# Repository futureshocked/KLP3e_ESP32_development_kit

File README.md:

# KLP3e ESP32 development kit, a Kicad project

This is the repository for the "ESP32 Devkit clone" project.

This is one of the projects from the course [KiCad Like a Pro, 3rd edition](https://techexplorations.com/so/kicad-like-a-pro-3rd-edition/).

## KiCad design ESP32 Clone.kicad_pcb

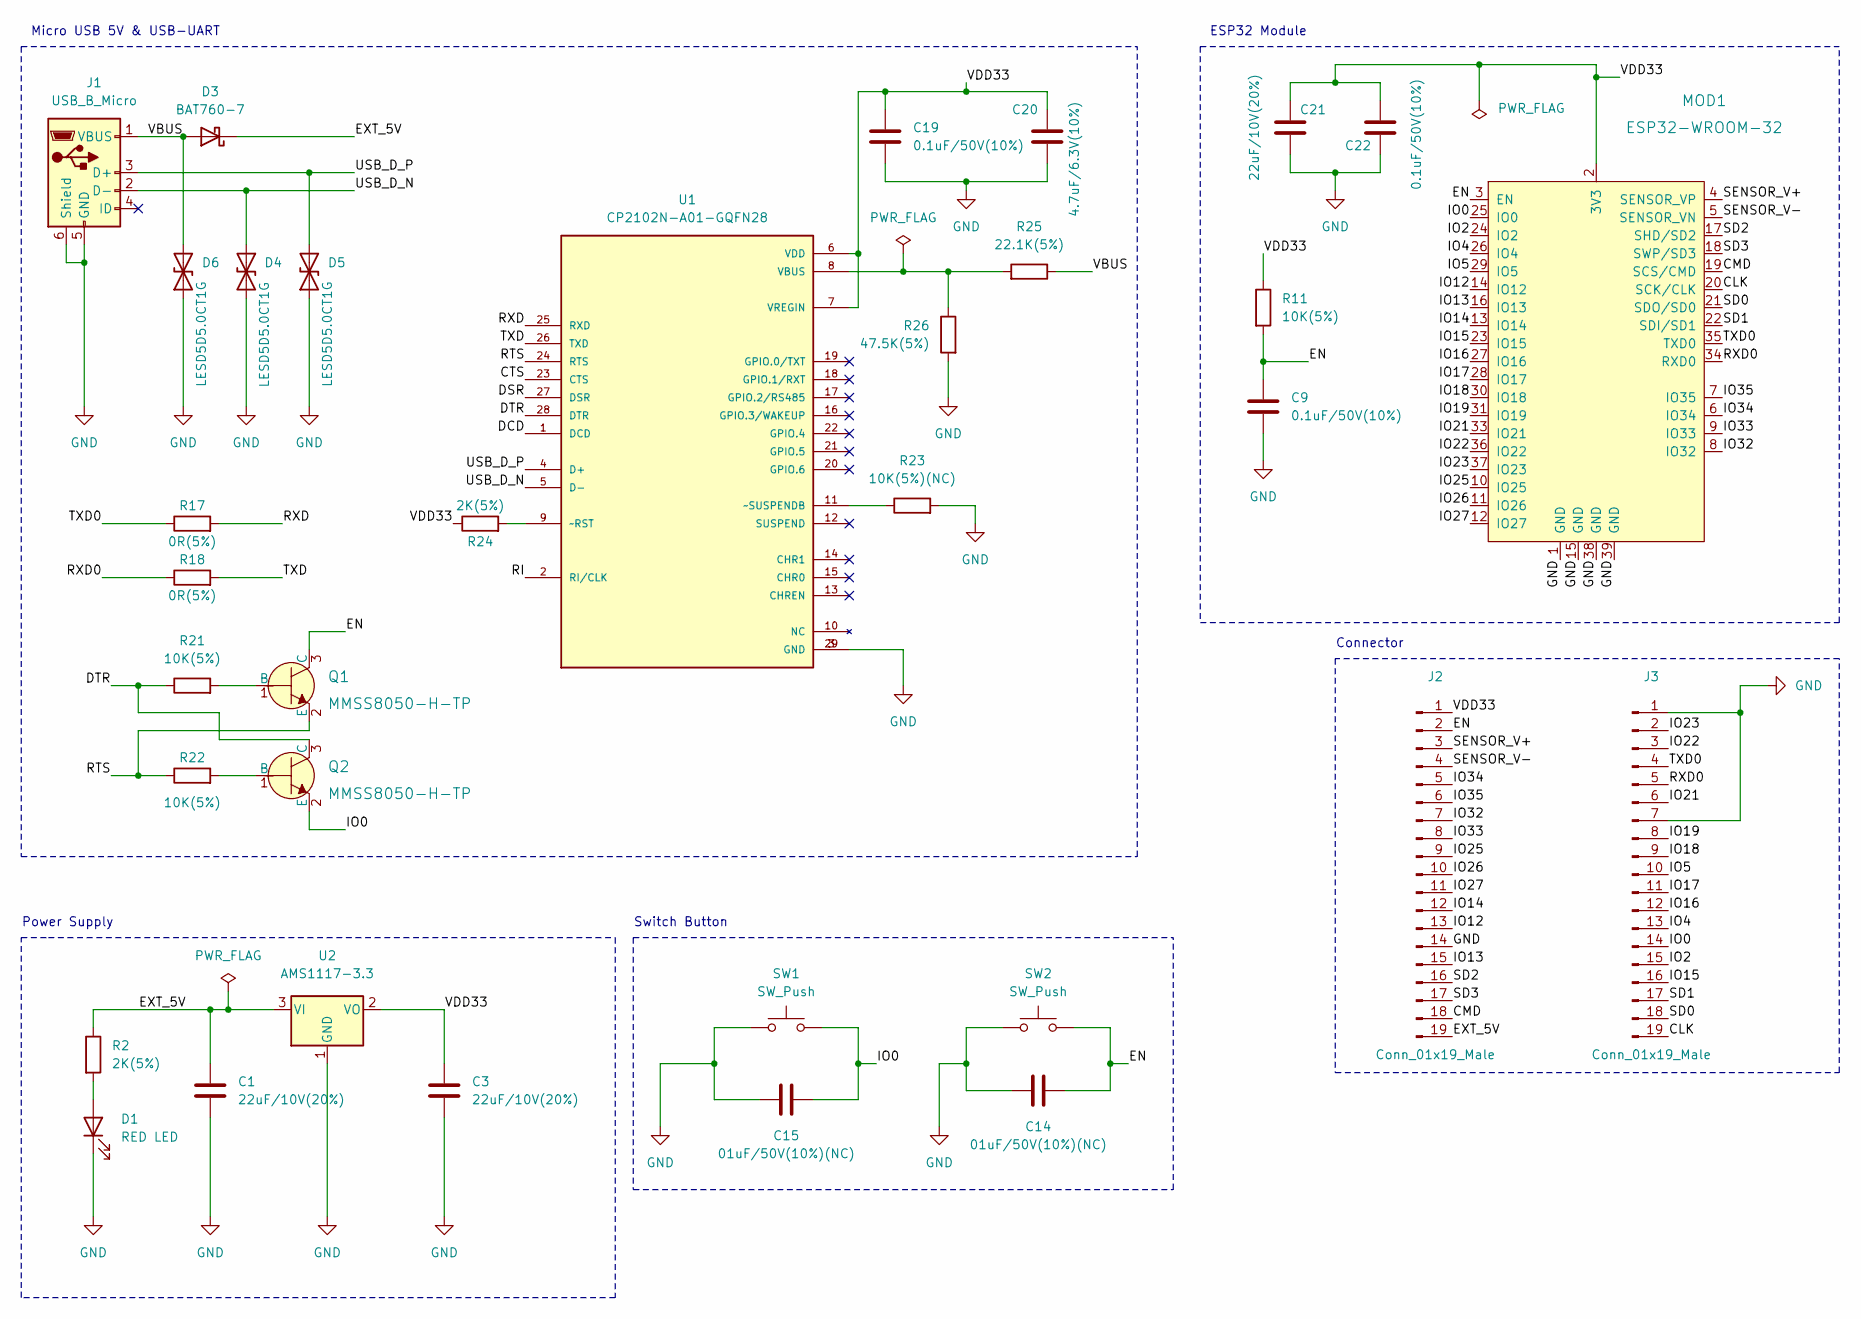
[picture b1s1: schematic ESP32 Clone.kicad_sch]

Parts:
C1, C3, C21: 22uF/10V(20%); C_0603_1608Metric
C9, C19, C22: 0.1uF/50V(10%); C_0402_1005Metric
C14, C15: 01uF/50V(10%)(NC); C_0402_1005Metric
C20: 4.7uF/6.3V(10%); C_0402_1005Metric
D1: RED LED; LED_0201_0603Metric
D3: BAT760-7; D_SOD-323
D4, D5, D6: LESD5D5.0CT1G; D_SOD-523
J1: USB_B_Micro; USB_Micro-AB_Molex_47590-0001
J2, J3: Conn_01x19_Male; PinHeader_1x19_P2.54mm_Vertical
MOD1: ESP32-WROOM-32; ESP32-WROOM-32D; MPN ESP32-WROOM-32; Digi-Key_PN 1904-1010-1-ND
Q1, Q2: MMSS8050-H-TP; SOT-23-3; MPN MMSS8050-H-TP; Digi-Key_PN MMSS8050-H-TPMSCT-ND
R2, R24: 2K(5%); R_01005_0402Metric
R11: 10K(5%); R_01005_0402Metric
R17, R18: 0R(5%); R_01005_0402Metric
R21, R22: 10K(5%); R_0402_1005Metric
R23: 10K(5%)(NC); R_01005_0402Metric
R25: 22.1K(5%); R_01005_0402Metric
R26: 47.5K(5%); R_01005_0402Metric
SW1, SW2: SW_Push; SW_B3S-1000P
U1: CP2102N-A01-GQFN28; TQFN-28-1EP_5x5mm_P0.5mm_EP2.7x2.7mm; PARTREV 1.0
U2: AMS1117-3.3; SOT-223-3_TabPin2

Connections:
/CLK: J3.19, MOD1.20 (SCK/CLK)
/CMD: J2.18, MOD1.19 (SCS/CMD)
/CTS: U1.23 (CTS)
/DCD: U1.1 (DCD)
/DSR: U1.27 (DSR)
/DTR: Q2.3 (C), R21.1, U1.28 (DTR)
/EN: C9.1, C14.2, J2.2, MOD1.3 (EN), Q1.3 (C), R11.2, SW2.2
/EXT_5V: C1.1, D3.1 (K), J2.19, R2.1, U2.3 (VI)
/IO0: C15.2, J3.14, MOD1.25 (IO0), Q2.2 (E), SW1.2
/IO2: J3.15, MOD1.24 (IO2)
/IO4: J3.13, MOD1.26 (IO4)
/IO5: J3.10, MOD1.29 (IO5)
/IO12: J2.13, MOD1.14 (IO12)
/IO13: J2.15, MOD1.16 (IO13)
/IO14: J2.12, MOD1.13 (IO14)
/IO15: J3.16, MOD1.23 (IO15)
/IO16: J3.12, MOD1.27 (IO16)
/IO17: J3.11, MOD1.28 (IO17)
/IO18: J3.9, MOD1.30 (IO18)
/IO19: J3.8, MOD1.31 (IO19)
/IO21: J3.6, MOD1.33 (IO21)
/IO22: J3.3, MOD1.36 (IO22)
/IO23: J3.2, MOD1.37 (IO23)
/IO25: J2.9, MOD1.10 (IO25)
/IO26: J2.10, MOD1.11 (IO26)
/IO27: J2.11, MOD1.12 (IO27)
/IO32: J2.7, MOD1.8 (IO32)
/IO33: J2.8, MOD1.9 (IO33)
/IO34: J2.5, MOD1.6 (IO34)
/IO35: J2.6, MOD1.7 (IO35)
/RI: U1.2 (RI/CLK)
/RTS: Q1.2 (E), R22.1, U1.24 (RTS)
/RXD: R17.2, U1.25 (RXD)
/RXD0: J3.5, MOD1.34 (RXD0), R18.1
/SD0: J3.18, MOD1.21 (SDO/SD0)
/SD1: J3.17, MOD1.22 (SDI/SD1)
/SD2: J2.16, MOD1.17 (SHD/SD2)
/SD3: J2.17, MOD1.18 (SWP/SD3)
/SENSOR_V+: J2.3, MOD1.4 (SENSOR_VP)
/SENSOR_V-: J2.4, MOD1.5 (SENSOR_VN)
/TXD: R18.2, U1.26 (TXD)
/TXD0: J3.4, MOD1.35 (TXD0), R17.1
/USB_D_N: D4.1 (A1), J1.2 (D-), U1.5 (D-)
/USB_D_P: D5.2 (A2), J1.3 (D+), U1.4 (D+)
/VBUS: D3.2 (A), D6.2 (A2), J1.1 (VBUS), R25.1
/VDD33: C3.1, C19.1, C20.1, C21.1, C22.1, J2.1, MOD1.2 (3V3), R11.1, R24.1, U1.6 (VDD), U1.7 (VREGIN), U2.2 (VO)
GND: C1.2, C3.2, C9.2, C14.1, C15.1, C19.2, C20.2, C21.2, C22.2, D1.1 (K), D4.2 (A2), D5.1 (A1), D6.1 (A1), J1.5 (GND), J1.6 (Shield), J2.14, J3.1, J3.7, MOD1.1 (GND), MOD1.15 (GND), MOD1.38 (GND), MOD1.39 (GND), R23.2, R26.2, SW1.1, SW2.1, U1.3 (GND), U1.29 (GND), U2.1 (GND)
unnamed: R25.2, R26.1, U1.8 (VBUS)
unnamed: D1.2 (A), R2.2
unnamed: Q1.1 (B), R21.2
unnamed: Q2.1 (B), R22.2
unnamed: R24.2, U1.9 (~RST)
unnamed: R23.1, U1.11 (~SUSPENDB)

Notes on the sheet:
Micro USB 5V & USB-UART
Connector
Power Supply
Switch Button
ESP32 Module

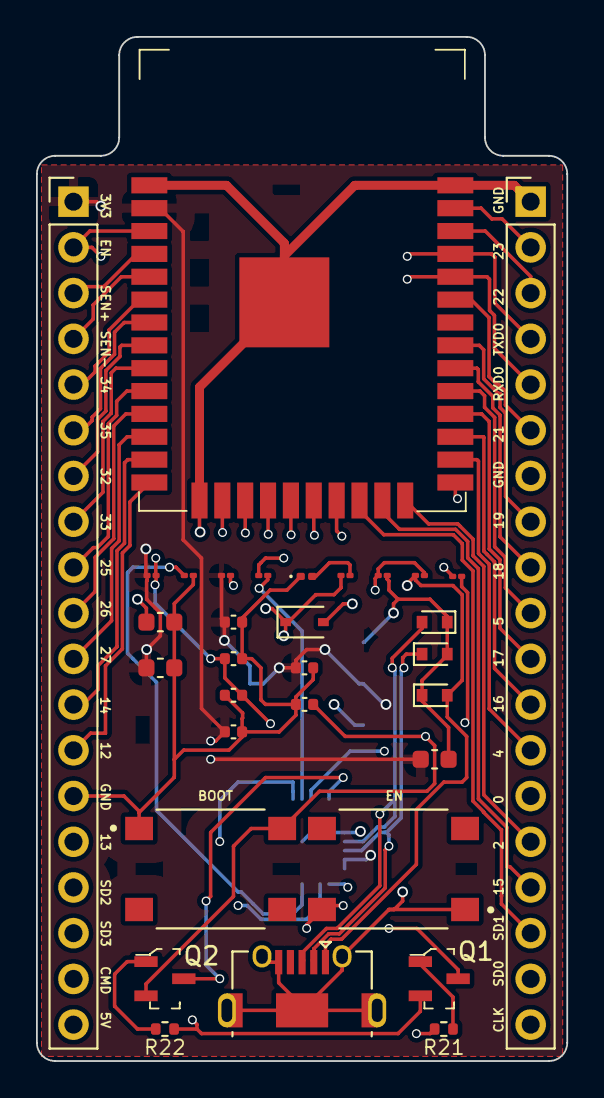
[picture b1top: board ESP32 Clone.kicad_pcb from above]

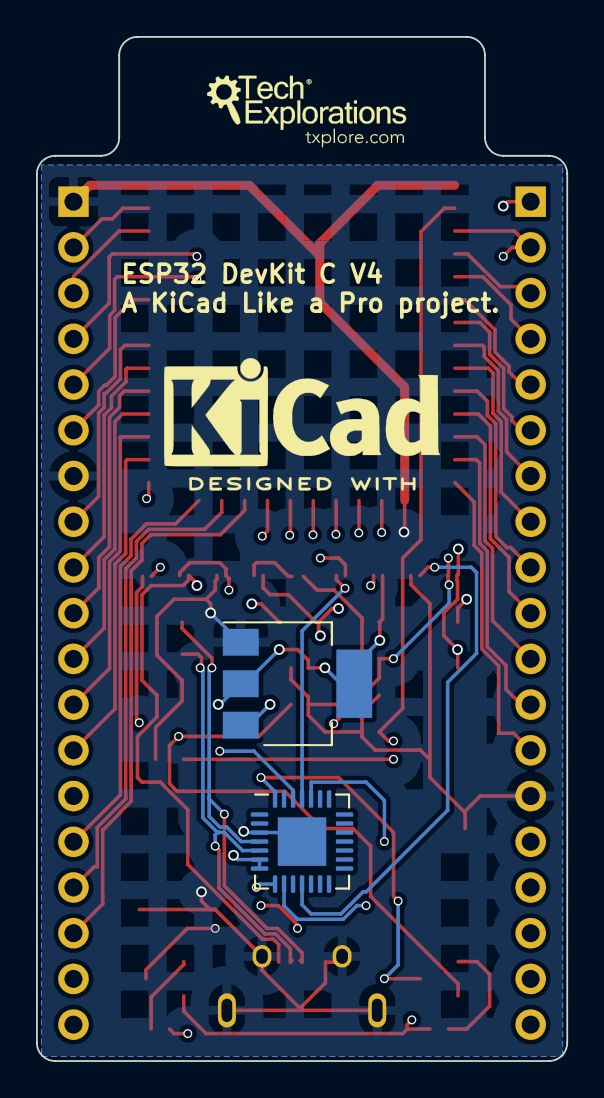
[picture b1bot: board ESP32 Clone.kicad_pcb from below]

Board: 4 copper layers, 29.5 x 56.9 mm, 35 parts (3 on the bottom side), 49 nets.

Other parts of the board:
G1: LOGO; TE_Logo_11.6x4

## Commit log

2023-04-03 Fixed bug in pin 2 of ESP32 module
